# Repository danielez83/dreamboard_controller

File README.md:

# dreamboard_controller
**arduino src** Code for arduino dreamboard controller (V alpha 0)
**pcb** Kicad project (schematics, pcb)

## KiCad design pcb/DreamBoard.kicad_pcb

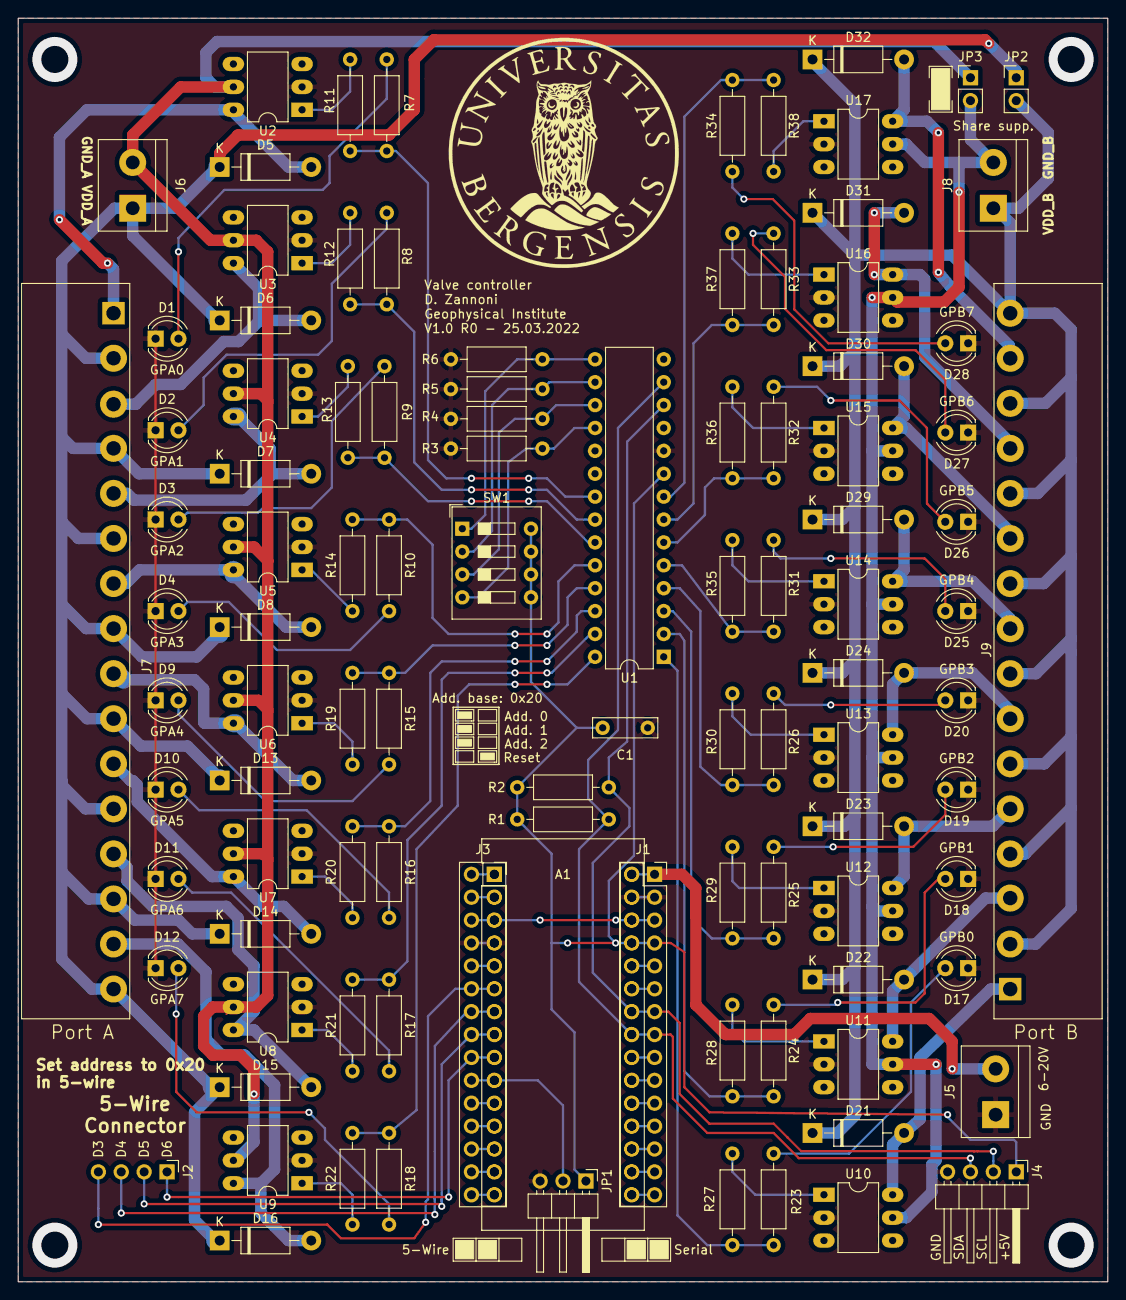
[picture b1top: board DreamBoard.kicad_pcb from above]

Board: 2 copper layers, 120.9 x 140.2 mm, 102 parts (0 on the bottom side), 100 nets.

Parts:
A1: Arduino_Nano_v2.x; Arduino_Nano
C1: C; C_Rect_L7.0mm_W2.0mm_P5.00mm
D1: GPA0; LED_D4.0mm
D2: GPA1; LED_D4.0mm
D3: GPA2; LED_D4.0mm
D4: GPA3; LED_D4.0mm
D5, D6, D7, D8, D13, D14, D15, D16, D21, D22, D23, D24, D29, D30, D31, D32: 1N4005; D_DO-41_SOD81_P10.16mm_Horizontal
D9: GPA4; LED_D4.0mm
D10: GPA5; LED_D4.0mm
D11: GPA6; LED_D4.0mm
D12: GPA7; LED_D4.0mm
D17: GPB0; LED_D4.0mm
D18: GPB1; LED_D4.0mm
D19: GPB2; LED_D4.0mm
D20: GPB3; LED_D4.0mm
D25: GPB4; LED_D4.0mm
D26: GPB5; LED_D4.0mm
D27: GPB6; LED_D4.0mm
D28: GPB7; LED_D4.0mm
J1: Arduino_LeftSide; PinSocket_2x15_P2.54mm_Vertical
J2: 5-W control; PinHeader_1x04_P2.54mm_Horizontal
J3: Arduino_RightSide; PinSocket_2x15_P2.54mm_Vertical
J4: I2C bus connector; PinHeader_1x04_P2.54mm_Horizontal
J5: External PS; TerminalBlock_bornier-2_P5.08mm
J6: PS Relay A; TerminalBlock_bornier-2_P5.08mm
J7: GPA Valves Conn; 1-2350513-6
J8: PS Relay B; TerminalBlock_bornier-2_P5.08mm
J9: GPB Valves Conn; 1-2350513-6
JP1: SolderJumper_3_Open; PinHeader_1x03_P2.54mm_Horizontal
JP2: Vdrive_relay Jumper; PinHeader_1x02_P2.54mm_Vertical
JP3: GND_relay Jumper; PinHeader_1x02_P2.54mm_Vertical
R1, R2: 1k; R_Axial_DIN0207_L6.3mm_D2.5mm_P10.16mm_Horizontal
R3, R4: 10k; R_Axial_DIN0207_L6.3mm_D2.5mm_P10.16mm_Horizontal
R5, R6: R; R_Axial_DIN0207_L6.3mm_D2.5mm_P10.16mm_Horizontal
R7, R8, R9, R10, R15, R16, R17, R18, R23, R24, R25, R26, R31, R32, R33, R34: 220; R_Axial_DIN0207_L6.3mm_D2.5mm_P10.16mm_Horizontal
R11, R12, R13, R14, R19, R20, R21, R22, R27, R28, R29, R30, R35, R36, R37, R38: 680; R_Axial_DIN0207_L6.3mm_D2.5mm_P10.16mm_Horizontal
SW1: MCP ADD selector; SW_DIP_SPSTx04_Slide_9.78x12.34mm_W7.62mm_P2.54mm
U1: MCP23017_SP; DIP-28_W7.62mm
U2, U3, U4, U5, U6, U7, U8, U9, U10, U11, U12, U13, U14, U15, U16, U17: AQV252G; DIP-6_W7.62mm_LongPads

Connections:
+3V3: A1.17, J1.27, J1.28
+5V: A1.27, C1.2, J1.7, J1.8, J4.1, JP1.1, R1.1, R2.1, SW1.5, SW1.6, SW1.7, SW1.8, U1.9
/A0: A1.19, J1.23, J1.24
/A1: A1.20, J1.21, J1.22
/A2: A1.21, J1.19, J1.20
/A3: A1.22, J1.17, J1.18
/A6: A1.25, J1.11, J1.12
/A7: A1.26, J1.9, J1.10
/AREF: A1.18, J1.25, J1.26
/D0: A1.2, J3.3, J3.4
/D1: A1.1, J3.1, J3.2
/D2: A1.5, J3.9, J3.10
/D3: A1.6, J2.4, J3.11, J3.12
/D4: A1.7, J2.3, J3.13, J3.14
/D5: A1.8, J2.2, J3.15, J3.16
/D6: A1.9, J2.1, J3.17, J3.18
/D7: A1.10, J3.19, J3.20, JP1.2
/D8: A1.11, J3.21, J3.22
/D9: A1.12, J3.23, J3.24
/D10: A1.13, J3.25, J3.26
/D11: A1.14, J3.27, J3.28
/D12: A1.15, J3.29, J3.30
/D13: A1.16, J1.29, J1.30
/RESET: A1.3, A1.28, J1.5, J1.6, J3.5, J3.6
GND: A1.4, A1.29, C1.1, D1.1, D2.1, D3.1, D4.1, D9.1, D10.1, D11.1, D12.1, D17.1, D18.1, D19.1, D20.1, D25.1, D26.1, D27.1, D28.1, J1.3, J1.4, J3.7, J3.8, J4.4, J5.1, JP1.3, R3.2, R4.2, R5.2, R6.2, U1.10, U2.2, U3.2, U4.2, U5.2, U6.2, U7.2, U8.2, U9.2, U10.2, U11.2, U12.2, U13.2, U14.2, U15.2, U16.2, U17.2
GND_A: J6.2, JP3.1, U2.5, U3.5, U4.5, U5.5, U6.5, U7.5, U8.5, U9.5
GND_B: J8.2, JP3.2, U10.5, U11.5, U12.5, U13.5, U14.5, U15.5, U16.5, U17.5
GPA0: R7.1, R11.2, U1.21
GPA1: R8.1, R12.2, U1.22
GPA2: R9.1, R13.2, U1.23
GPA3: R10.1, R14.2, U1.24
GPA4: R15.1, R19.2, U1.25
GPA5: R16.1, R20.2, U1.26
GPA6: R17.1, R21.2, U1.27
GPA7: R18.1, R22.2, U1.28
GPB0: R23.1, R27.2, U1.1
GPB1: R24.1, R28.2, U1.2
GPB2: R25.1, R29.2, U1.3
GPB3: R26.1, R30.2, U1.4
GPB4: R31.1, R35.2, U1.5
GPB5: R32.1, R36.2, U1.6
GPB6: R33.1, R37.2, U1.7
GPB7: R34.1, R38.2, U1.8
unnamed: D1.2, R7.2
unnamed: D2.2, R8.2
unnamed: D3.2, R9.2
unnamed: D4.2, R10.2
unnamed: D9.2, R15.2
unnamed: D10.2, R16.2
unnamed: D11.2, R17.2
unnamed: D12.2, R18.2
unnamed: D17.2, R23.2
unnamed: D18.2, R24.2
unnamed: D19.2, R25.2
unnamed: D20.2, R26.2
unnamed: D25.2, R31.2
unnamed: D26.2, R32.2
unnamed: D27.2, R33.2
unnamed: D28.2, R34.2
unnamed: R3.1, SW1.4, U1.18
unnamed: R4.1, SW1.3, U1.17
unnamed: R5.1, SW1.2, U1.16
unnamed: R6.1, SW1.1, U1.15
unnamed: R11.1, U2.1
unnamed: R12.1, U3.1
unnamed: R13.1, U4.1
unnamed: R14.1, U5.1
unnamed: R19.1, U6.1
unnamed: R20.1, U7.1
unnamed: R21.1, U8.1
unnamed: R22.1, U9.1
unnamed: R27.1, U10.1
unnamed: R28.1, U11.1
unnamed: R29.1, U12.1
unnamed: R30.1, U13.1
unnamed: R35.1, U14.1
unnamed: R36.1, U15.1
unnamed: R37.1, U16.1
unnamed: R38.1, U17.1
SCL: A1.24, J1.13, J1.14, J4.2, R2.2, U1.12
SDA: A1.23, J1.15, J1.16, J4.3, R1.2, U1.13
VDD: A1.30, J1.1, J1.2, J5.2
Valve_GPA0: D5.2, J7.1, U2.6
Valve_GPA1: D6.2, J7.3, U3.6
Valve_GPA2: D7.2, J7.5, U4.6
Valve_GPA3: D8.2, J7.7, U5.6
Valve_GPA4: D13.2, J7.9, U6.6
Valve_GPA5: D14.2, J7.11, U7.6
Valve_GPA6: D15.2, J7.13, U8.6
Valve_GPA7: D16.2, J7.15, U9.6
Valve_GPB0: D21.2, J9.1, U10.6
Valve_GPB1: D22.2, J9.3, U11.6
Valve_GPB2: D23.2, J9.5, U12.6
Valve_GPB3: D24.2, J9.7, U13.6
Valve_GPB4: D29.2, J9.9, U14.6
Valve_GPB5: D30.2, J9.11, U15.6
Valve_GPB6: D31.2, J9.13, U16.6
Valve_GPB7: D32.2, J9.15, U17.6
Vdrive_A: D5.1, D6.1, D7.1, D8.1, D13.1, D14.1, D15.1, D16.1, J6.1, J7.2, J7.4, J7.6, J7.8, J7.10, J7.12, J7.14, J7.16, JP2.1
Vdrive_B: D21.1, D22.1, D23.1, D24.1, D29.1, D30.1, D31.1, D32.1, J8.1, J9.2, J9.4, J9.6, J9.8, J9.10, J9.12, J9.14, J9.16, JP2.2

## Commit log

2022-03-25 First commit, code adjusted on 25 March 2022
2022-08-12 functions moved. Test function implemented. Mode selection enabled. Read commands from serial
2022-08-13 port function included
2022-08-16 Read port status. Working on 5 wire mode.
2022-10-16 PCB upload
2022-10-16 README update
2024-05-30 Update dreamboard_controller.ino
    Add multi-board support
